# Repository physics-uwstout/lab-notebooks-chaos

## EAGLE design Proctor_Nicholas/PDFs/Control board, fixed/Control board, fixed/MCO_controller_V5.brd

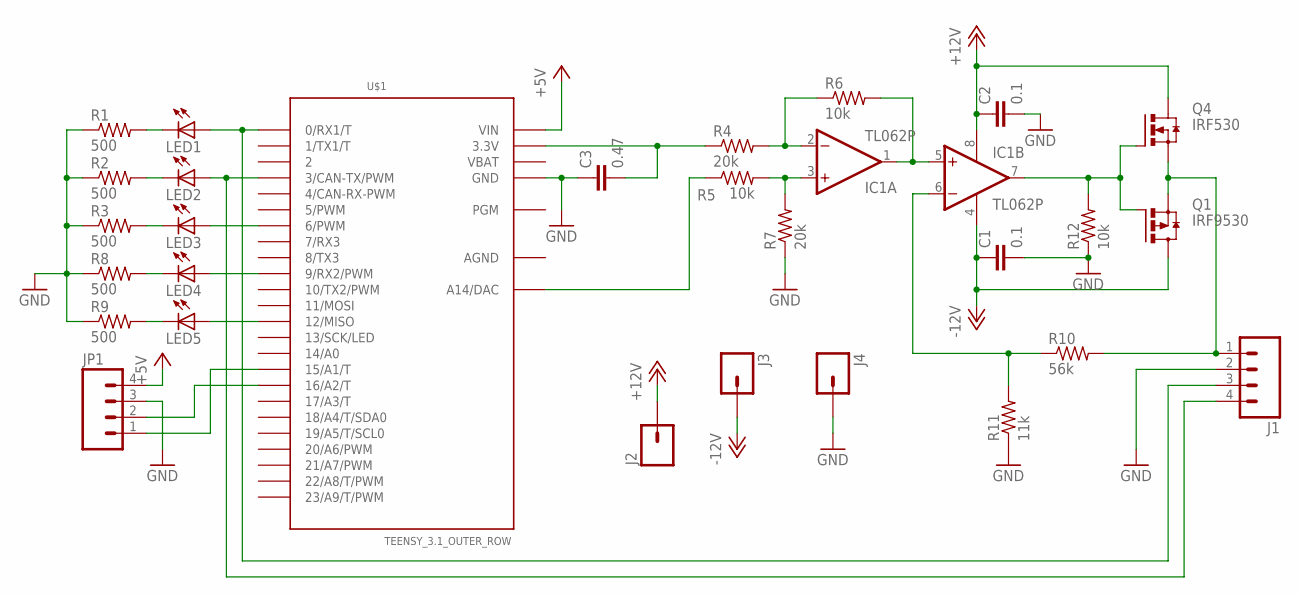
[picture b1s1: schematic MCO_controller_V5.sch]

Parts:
C1, C2: 0.1; CAP-PTH-SMALL
C3: 0.47; CAP-PTH-5MM
IC1: TL062P; DIL08
J1: M04SCREW; SCREWTERMINAL-3.5MM-4
J2, J3, J4: M01PTH_LONGPAD; 1X01_LONGPAD
JP1: M04SCREW; SCREWTERMINAL-3.5MM-4
LED1, LED2, LED3, LED4, LED5: LED5MM
Q1: IRF9530; TO220AV
Q4: IRF530; TO220AV
R1, R2, R3, R8, R9: 500; 0207/10
R4, R7: 20k; 0207/10
R5, R6, R12: 10k; 0207/10
R10: 56k; 0207/10
R11: 11k; 0207/10
U$1: TEENSY_3.1_OUTER_ROW; TEENSY3-OUTER_ROW

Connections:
+5V: JP1.4, U$1.VIN
+12V: C2.1, IC1.8 (V+), J2.1, Q4.C (D)
-12V: C1.1, IC1.4 (V-), J3.1, Q1.C (D)
AGND: U$1.AGND
GND: C1.2, C2.2, C3.1, J1.2, J4.1, JP1.3, R1.1, R2.1, R3.1, R7.1, R8.1, R9.1, R11.1, R12.1, U$1.GND, U$1.GND1 (GND)
unnamed: IC1.1 (OUT), IC1.5 (+IN), R6.2
unnamed: IC1.2 (-IN), R4.2, R6.1
unnamed: IC1.3 (+IN), R5.2, R7.2
unnamed: C3.2, R4.1, U$1.3.3V, U$1.3.3V1 (3.3V)
unnamed: IC1.7 (OUT), Q1.B (G), Q4.B (G), R12.2
unnamed: JP1.1, U$1.15/A1 (15/A1/T)
unnamed: R5.1, U$1.RESET/DAC (A14/DAC)
unnamed: LED4.A, U$1.9 (9/RX2/PWM)
unnamed: JP1.2, U$1.16/A2 (16/A2/T)
unnamed: LED1.K (C), R1.2
unnamed: LED2.K (C), R2.2
unnamed: LED3.K (C), R3.2
unnamed: J1.4, LED2.A, U$1.3 (3/CAN-TX/PWM)
unnamed: J1.3, LED1.A, U$1.0 (0/RX1/T)
unnamed: LED3.A, U$1.6 (6/PWM)
unnamed: LED4.K (C), R8.2
unnamed: LED5.A, U$1.12 (12/MISO)
unnamed: LED5.K (C), R9.2
unnamed: J1.1, Q1.E (S), Q4.E (S), R10.2
unnamed: IC1.6 (-IN), R10.1, R11.2
VBAT: U$1.VBAT

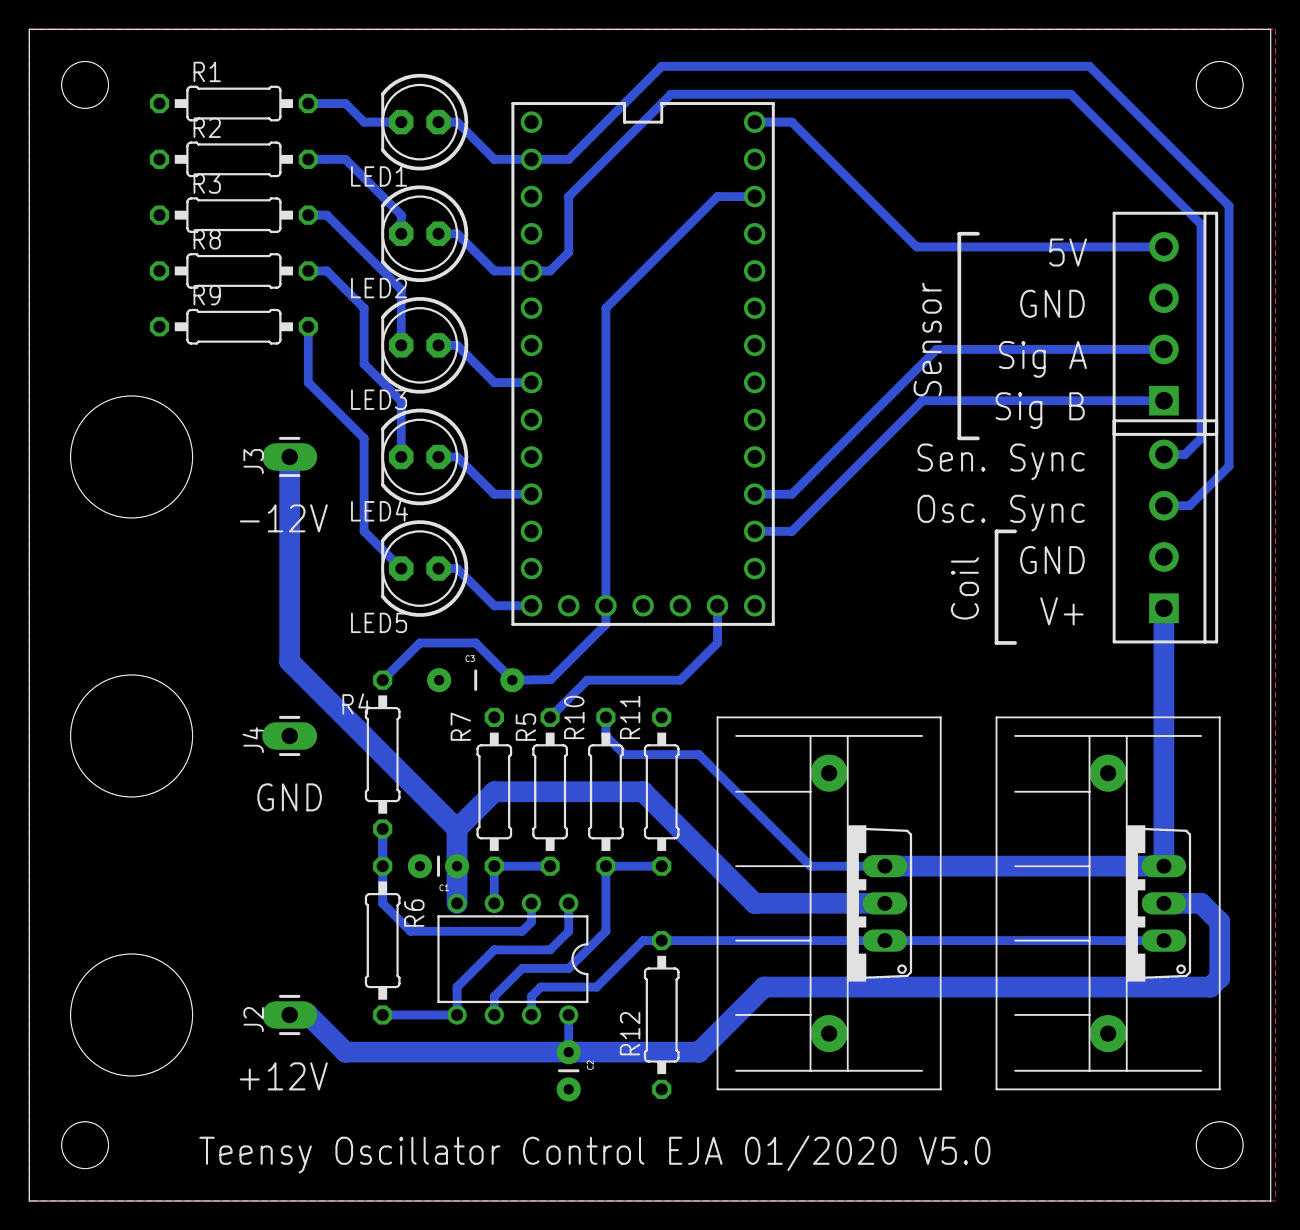
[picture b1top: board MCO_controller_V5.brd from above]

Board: 2 copper layers, 84.8 x 80.0 mm, 29 parts (0 on the bottom side), 24 nets.

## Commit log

2024-02-15 Setting up GitHub Classroom Feedback
2024-02-15 GitHub Classroom Feedback
2024-02-15 add online IDE url
2024-02-15 Nicholas's Lab Notebook
    Added Phys139 Notebook
2024-02-15 Lab notebook files copied
    2/15/2024
2024-02-15 Moved Rand File
    Moved Rand File
2024-02-15 jhdfkal
2024-02-15 2-15-2024 changes
2024-02-15 2/15/2024
    Notebook Entry
2024-02-20 2024-02-20
2024-02-22 changes as of 2/22/2024
2024-02-22 2024/02/22 - Notebook
2024-02-23 Graphs
2024-02-27 2024/02/27 Notebook Push
2024-02-27 2-27-2024
2024-02-29 2-29-2024
2024-02-29 2024-02-29 Notebook Push
2024-03-05 Notebook Push 2024-03-05
2024-03-08 3-7-2024
2024-03-21 3/21/2024
2024-03-28 2024-03-28 Notebook Push
2024-03-28 3-28-2024
2024-04-09 4-9-2024
2024-04-10 Notebook Push 2024-04-09
2024-04-18 4-18-2024
2024-04-25 Notebook Push 2024-04-25
2024-04-25 4-24-2024
2024-04-30 Notebook Push 2024-04-30

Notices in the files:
parts and their libraries:
SparkFun: Licensing: CC v3.0 Share-Alike You are welcome to use this library for commercial purposes.
